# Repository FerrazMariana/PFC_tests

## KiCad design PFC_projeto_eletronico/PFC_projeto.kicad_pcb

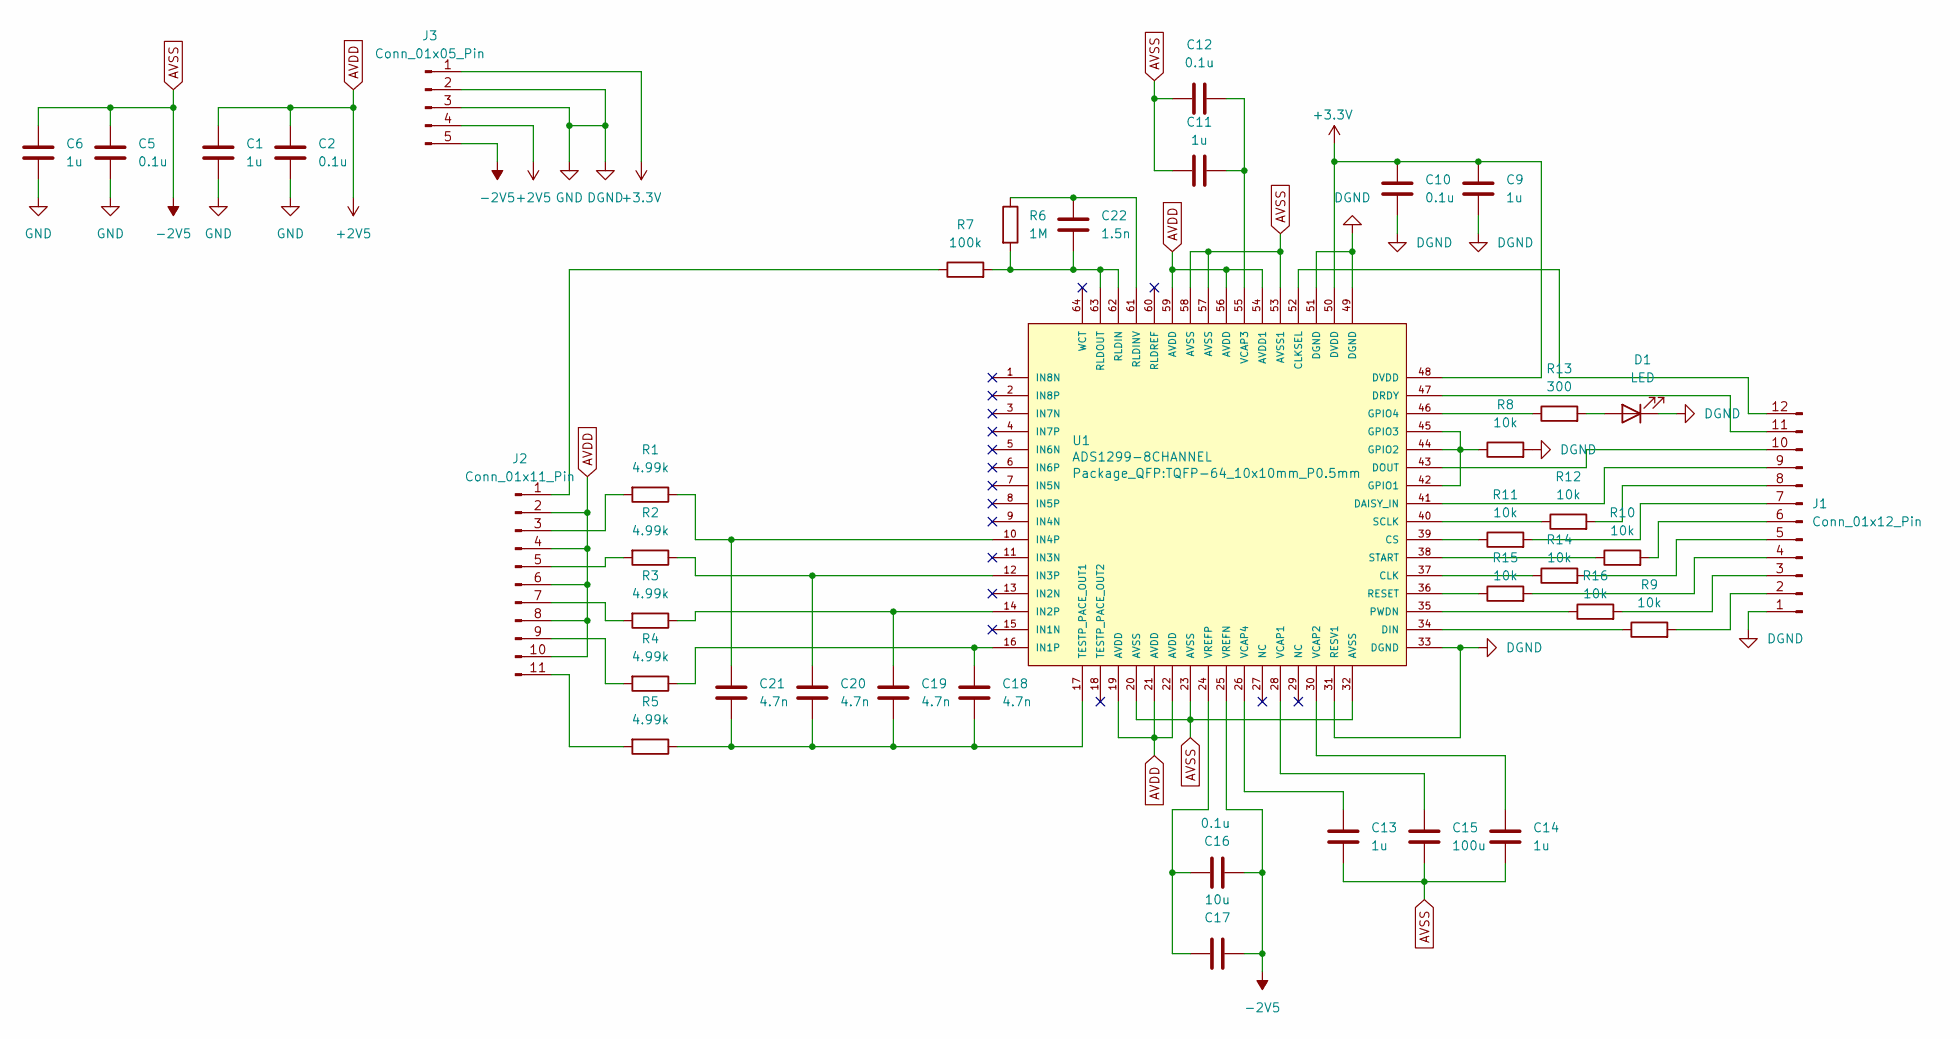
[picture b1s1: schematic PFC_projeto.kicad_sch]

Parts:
C1, C6, C9, C11, C13, C14: 1u; C_Disc_D6.0mm_W2.5mm_P5.00mm
C2, C5, C10, C12, C16: 0.1u; C_Disc_D6.0mm_W2.5mm_P5.00mm
C15: 100u; C_Disc_D6.0mm_W2.5mm_P5.00mm
C17: 10u; C_Disc_D6.0mm_W2.5mm_P5.00mm
C18, C19, C20, C21: 4.7n; C_Disc_D6.0mm_W2.5mm_P5.00mm
C22: 1.5n; C_Disc_D6.0mm_W2.5mm_P5.00mm
D1: LED; LED_D3.0mm
J1: Conn_01x12_Pin; PinHeader_1x12_P2.54mm_Vertical
J2: Conn_01x11_Pin; PinHeader_1x11_P2.54mm_Vertical
J3: Conn_01x05_Pin; TerminalBlock_Phoenix_MKDS-1,5-5_1x05_P5.00mm_Horizontal
R1, R2, R3, R4, R5: 4.99k; R_Axial_DIN0204_L3.6mm_D1.6mm_P7.62mm_Horizontal
R6: 1M; R_Axial_DIN0204_L3.6mm_D1.6mm_P7.62mm_Horizontal
R7: 100k; R_Axial_DIN0204_L3.6mm_D1.6mm_P7.62mm_Horizontal
R8, R9, R10, R11, R12, R14, R15, R16: 10k; R_Axial_DIN0204_L3.6mm_D1.6mm_P7.62mm_Horizontal
R13: 300; R_Axial_DIN0204_L3.6mm_D1.6mm_P7.62mm_Horizontal
U1: ADS1299-8CHANNEL; TQFP-64_10x10mm_P0.5mm

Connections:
+3.3V: C9.1, C10.1, J3.1, U1.48 (DVDD), U1.50 (DVDD)
AVDD: C1.1, C2.1, J2.2, J2.4, J2.6, J2.8, J2.10, J3.4, U1.19 (AVDD), U1.21 (AVDD), U1.22 (AVDD), U1.54 (AVDD1), U1.56 (AVDD), U1.59 (AVDD)
AVSS: C5.1, C6.1, C11.2, C12.2, C13.2, C14.2, C15.2, C16.2, C17.2, J3.5, U1.20 (AVSS), U1.23 (AVSS), U1.25 (VREFN), U1.32 (AVSS), U1.53 (AVSS1), U1.57 (AVSS), U1.58 (AVSS)
DGND: C1.2, C2.2, C5.2, C6.2, C9.2, C10.2, D1.1 (K), J1.1, J3.2, J3.3, R8.2, U1.31 (RESV1), U1.33 (DGND), U1.49 (DGND), U1.51 (DGND)
unnamed: D1.2 (A), R13.2
unnamed: J1.2, R9.2
unnamed: J1.3, R16.2
unnamed: J1.4, R15.2
unnamed: J1.5, R14.2
unnamed: J1.6, R10.2
unnamed: J1.7, R11.2
unnamed: J1.8, R12.2
unnamed: J1.9, U1.41 (DAISY_IN)
unnamed: J1.10, U1.43 (DOUT)
unnamed: J1.11, U1.47 (DRDY)
unnamed: J1.12, U1.52 (CLKSEL)
unnamed: J2.1, R7.1
unnamed: J2.3, R1.2
unnamed: J2.5, R2.2
unnamed: J2.7, R3.2
unnamed: J2.9, R4.2
unnamed: J2.11, R5.2
unnamed: R14.1, U1.37 (CLK)
unnamed: R11.1, U1.39 (CS)
unnamed: R9.1, U1.34 (DIN)
unnamed: R8.1, U1.42 (GPIO1), U1.44 (GPIO2), U1.45 (GPIO3)
unnamed: R13.1, U1.46 (GPIO4)
unnamed: C18.1, R4.1, U1.16 (IN1P)
unnamed: C19.1, R3.1, U1.14 (IN2P)
unnamed: C20.1, R2.1, U1.12 (IN3P)
unnamed: C21.1, R1.1, U1.10 (IN4P)
unnamed: R16.1, U1.35 (PWDN)
unnamed: R15.1, U1.36 (RESET)
unnamed: C22.2, R6.2, R7.2, U1.62 (RLDIN), U1.63 (RLDOUT)
unnamed: C22.1, R6.1, U1.61 (RLDINV)
unnamed: R12.1, U1.40 (SCLK)
unnamed: R10.1, U1.38 (START)
unnamed: C18.2, C19.2, C20.2, C21.2, R5.1, U1.17 (TESTP_PACE_OUT1)
unnamed: C15.1, U1.28 (VCAP1)
unnamed: C14.1, U1.30 (VCAP2)
unnamed: C11.1, C12.1, U1.55 (VCAP3)
unnamed: C13.1, U1.26 (VCAP4)
unnamed: C16.1, C17.1, U1.24 (VREFP)

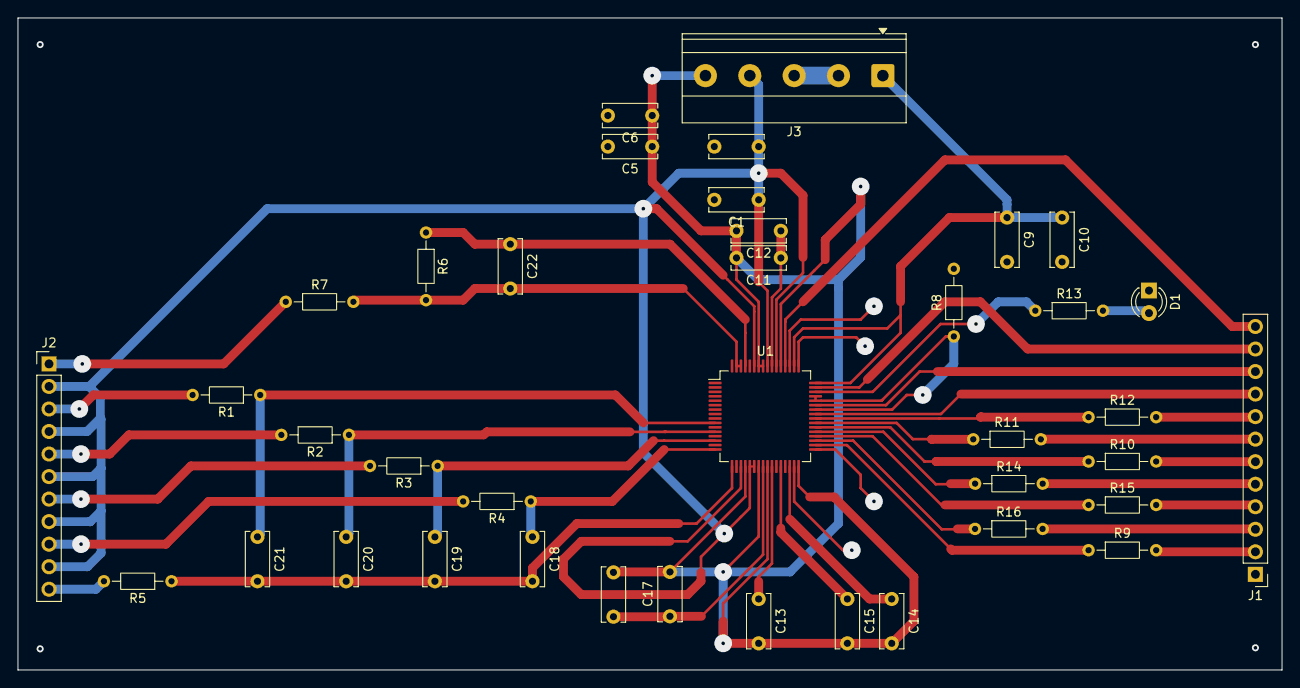
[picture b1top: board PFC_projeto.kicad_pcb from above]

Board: 2 copper layers, 142.5 x 73.5 mm, 39 parts (0 on the bottom side), 43 nets.

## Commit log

2026-01-20 Add files via upload
    ATUALIZAÇÃO
2026-01-20 teste
2026-01-20 test2
2026-01-26 pasta com os dados
2026-01-28 Modelos e dataset
2026-02-06 Treinamento_dados_crus
2026-03-10 Organizacao+CNN
2026-03-18 atualizacao_modelos_dataset
2026-03-26 Medicao dos tempos
2026-04-26 Adicionado as pastas com os códigos do sensor mpu e do ads1299
2026-05-08 Organização e limpeza
